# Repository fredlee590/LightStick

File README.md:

# LightStick

A short stick with LEDs and an IMU in it. Modulate, change color, etc based on movement. Should be a good show.

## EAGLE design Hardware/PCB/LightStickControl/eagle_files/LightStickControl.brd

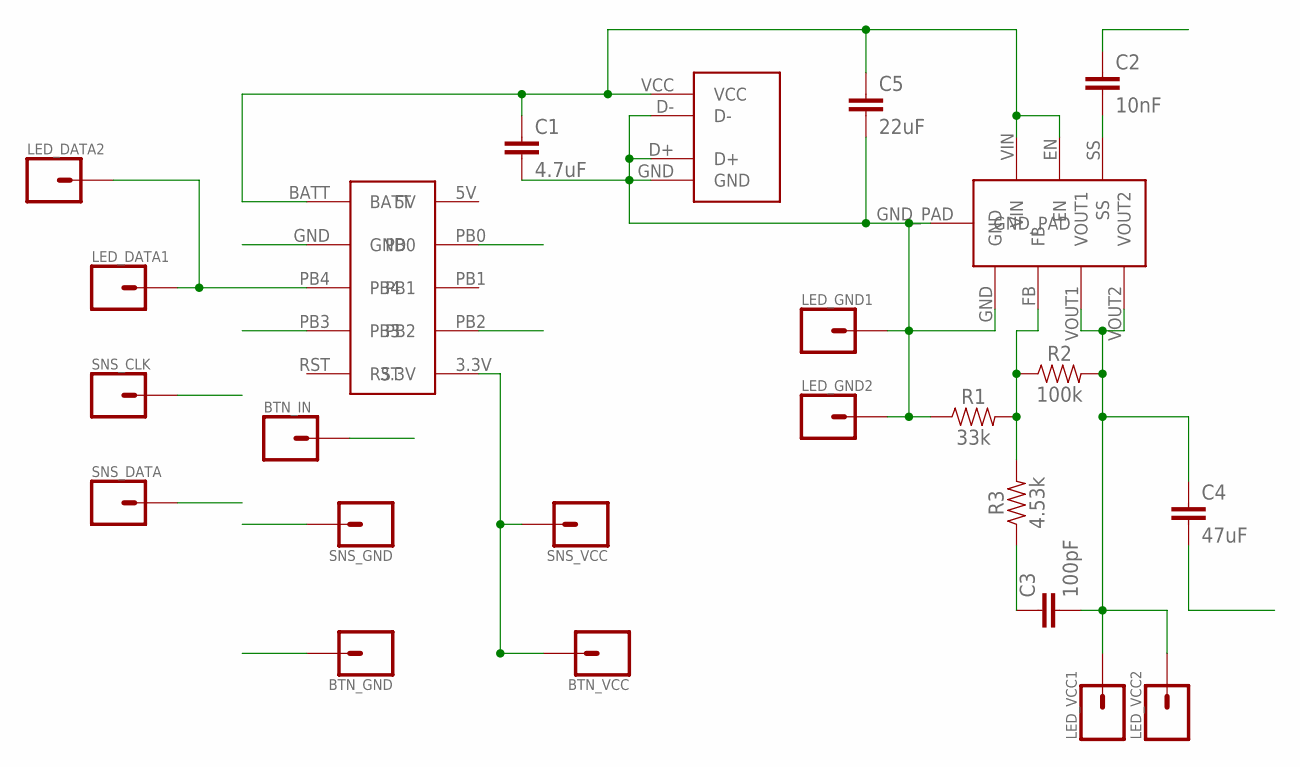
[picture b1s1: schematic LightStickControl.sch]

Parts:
BTN_GND: CONN_01; 1X01
BTN_IN: CONN_01; 1X01
BTN_VCC: CONN_01; 1X01
C1: 4.7uF; 0603
C2: 10nF; 0603
C3: 100pF; 0603
C4: 47uF; 0805
C5: 22uF; 0805
LED_DATA1, LED_DATA2: CONN_01; 1X01
LED_GND1, LED_GND2: CONN_01; 1X01
LED_VCC1, LED_VCC2: CONN_01; 1X01
MCU1: ARDUINO_TRINKET
R1: 33k; 0603
R2: 100k; 0603
R3: 4.53k; 0603
SNS_CLK: CONN_01; 1X01
SNS_DATA: CONN_01; 1X01
SNS_GND: CONN_01; 1X01
SNS_VCC: CONN_01; 1X01
USB1: USB_A_932
V1: LMZ10503; TO-PMOD

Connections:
BTN_IN: BTN_IN.1, MCU1.PB3
FB: R1.2, R2.1, R3.2, V1.FB
GND: BTN_GND.1, C1.2, C2.1, C4.2, C5.2, LED_GND1.1, LED_GND2.1, MCU1.GND, R1.1, SNS_GND.1, USB1.D+, USB1.D-, USB1.GND, V1.GND, V1.GND_PAD
LED_DATA: LED_DATA1.1, LED_DATA2.1, MCU1.PB4
SNS_CLK: MCU1.PB2, SNS_CLK.1
SNS_DATA: MCU1.PB0, SNS_DATA.1
SNS_VCC: BTN_VCC.1, MCU1.3.3V, SNS_VCC.1
SS: C2.2, V1.SS
VCC_IN: C1.1, C5.1, MCU1.BATT, USB1.VCC, V1.EN, V1.VIN
VOUT: C3.2, C4.1, LED_VCC1.1, LED_VCC2.1, R2.2, V1.VOUT1, V1.VOUT2
VOUT_C: C3.1, R3.1

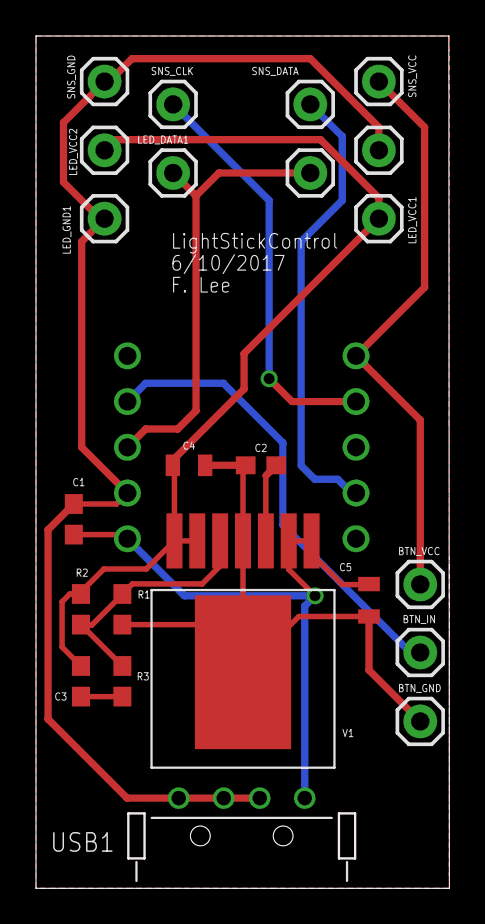
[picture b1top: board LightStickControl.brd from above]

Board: 2 copper layers, 22.8 x 47.2 mm, 24 parts (1 on the bottom side), 11 nets.

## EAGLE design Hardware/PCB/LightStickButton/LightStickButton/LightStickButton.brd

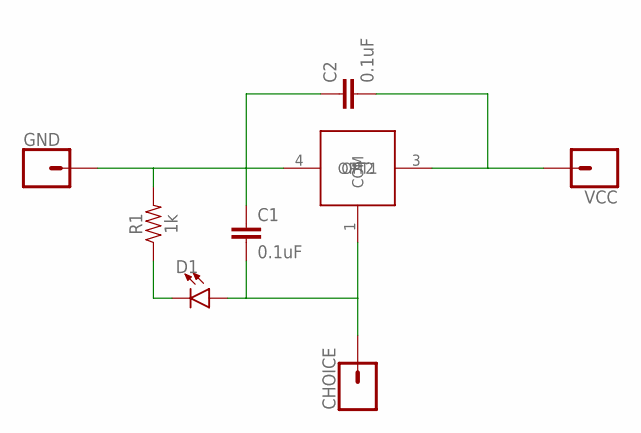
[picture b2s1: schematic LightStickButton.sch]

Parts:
B1: KS12R22CQD
C1, C2: 0.1uF; 0603
CHOICE: CONN_01; 1X01
D1: LED0603; LED-0603
GND: CONN_01; 1X01
R1: 1k; 0603
VCC: CONN_01; 1X01

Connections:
unnamed: B1.4 (OPT2), C1.1, C2.1, GND.1, R1.2
unnamed: B1.3 (OPT1), C2.2, VCC.1
unnamed: B1.1 (COM), C1.2, CHOICE.1, D1.A
unnamed: D1.C, R1.1

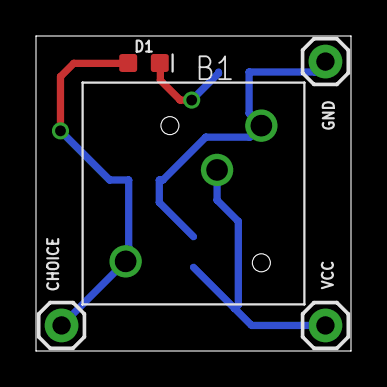
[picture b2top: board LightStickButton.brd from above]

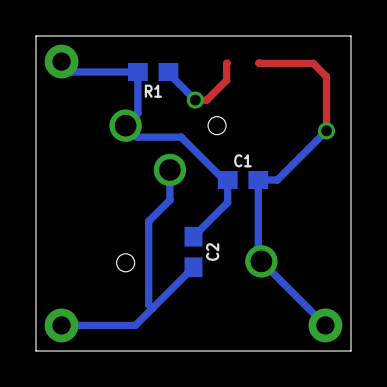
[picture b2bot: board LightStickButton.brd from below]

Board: 2 copper layers, 17.5 x 17.5 mm, 8 parts (3 on the bottom side), 4 nets.

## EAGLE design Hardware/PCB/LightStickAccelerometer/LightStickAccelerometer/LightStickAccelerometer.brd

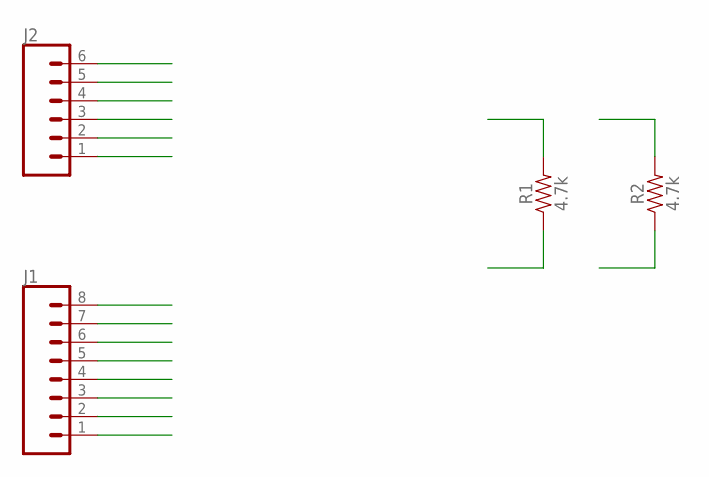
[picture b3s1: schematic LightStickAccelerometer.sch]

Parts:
J1: CONN_08"; 1X08
J2: CONN_06SILK_FEMALE_PTH; 1X06
R1, R2: 4.7k; 0603

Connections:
3VO: J1.3
GND: J1.2, J1.8, J2.6
INT1: J1.5, J2.5
INT2: J1.4, J2.4
SCL: J1.6, J2.2, R2.1
SDA: J1.7, J2.3, R1.1
VIN: J1.1, J2.1, R1.2, R2.2

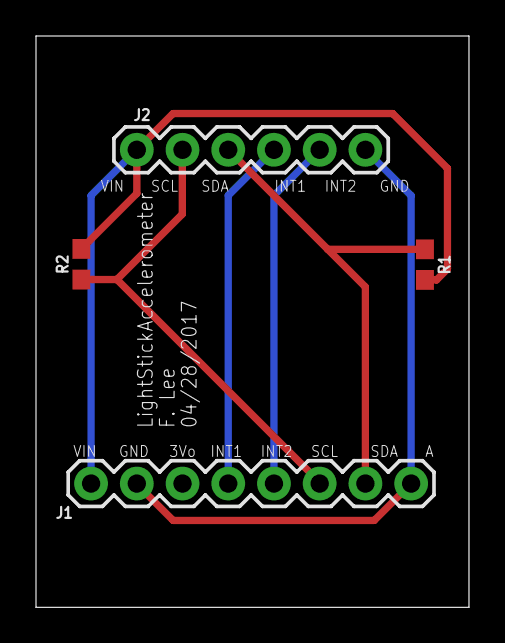
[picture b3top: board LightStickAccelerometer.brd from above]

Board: 2 copper layers, 24.1 x 31.7 mm, 4 parts (0 on the bottom side), 6 nets.

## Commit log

2017-03-08 Initial check in of LightStick project. Move to new format of Github.
2017-03-08 First cut of board layout. Add connectors. Label everything.
2017-03-09 Add support components and lay initial placement.
2017-03-09 Added routing.
2017-04-12 Shorten PCB to allow for a snug fit for the USB plug A
2017-04-17 Add 3D printed parts to maintain circuit board cohesion.
2017-04-19 Rebuild Tip Cap.
2017-04-19 Add folder for accelerometer PCB
2017-04-20 Planning for physical build out of the Light Stick blade and accelerometer circuit.
2017-04-20 Move LightStick blade from PCB directory to Laser cutting directory.
2017-04-25 Add rainbow fade for light stick
2017-04-28 Add LightStickAccelerometer schematic and board. Update eagle project file accordingly.
2017-04-28 Add slot for PCB
2017-04-28 Adjust PCB bounds.
2017-04-29 Move components to allow for some empty space on top and bottom.
2017-04-29 Use Laen's design rules in design rule check.
2017-05-08 Rename LaserCutting to reflect ends rather than means.
2017-05-08 Create directory for LightStickButtonPCB. Start with datasheet.
2017-05-08 Plan out Light stick button PCB.
2017-05-10 Create PCB for LightStick button.
2017-05-23 LightStickButton fixes. Holes moved to proper mirrored places. Through-holes widened.
2017-06-12 Add new switching voltage regulator.
2017-06-12 Add ground plane to top layer.
2017-06-29 Initial check in of accelerometer proof of concept. Can use it in lightweight manner. Add todo.
2019-10-14 Initial check in of basic Light Stick sketch
    Initial check in of simplest Light Stick sketch to use accelerometer in
    color determination.
2023-12-28 Import to KiCad
    Convert Eagle files into KiCad files for further development.

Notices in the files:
parts and their libraries:
SparkFun-Connectors: Licensing: Creative Commons ShareAlike 4.0 International - https://creativecommons.org/licenses/by-sa/4.0
